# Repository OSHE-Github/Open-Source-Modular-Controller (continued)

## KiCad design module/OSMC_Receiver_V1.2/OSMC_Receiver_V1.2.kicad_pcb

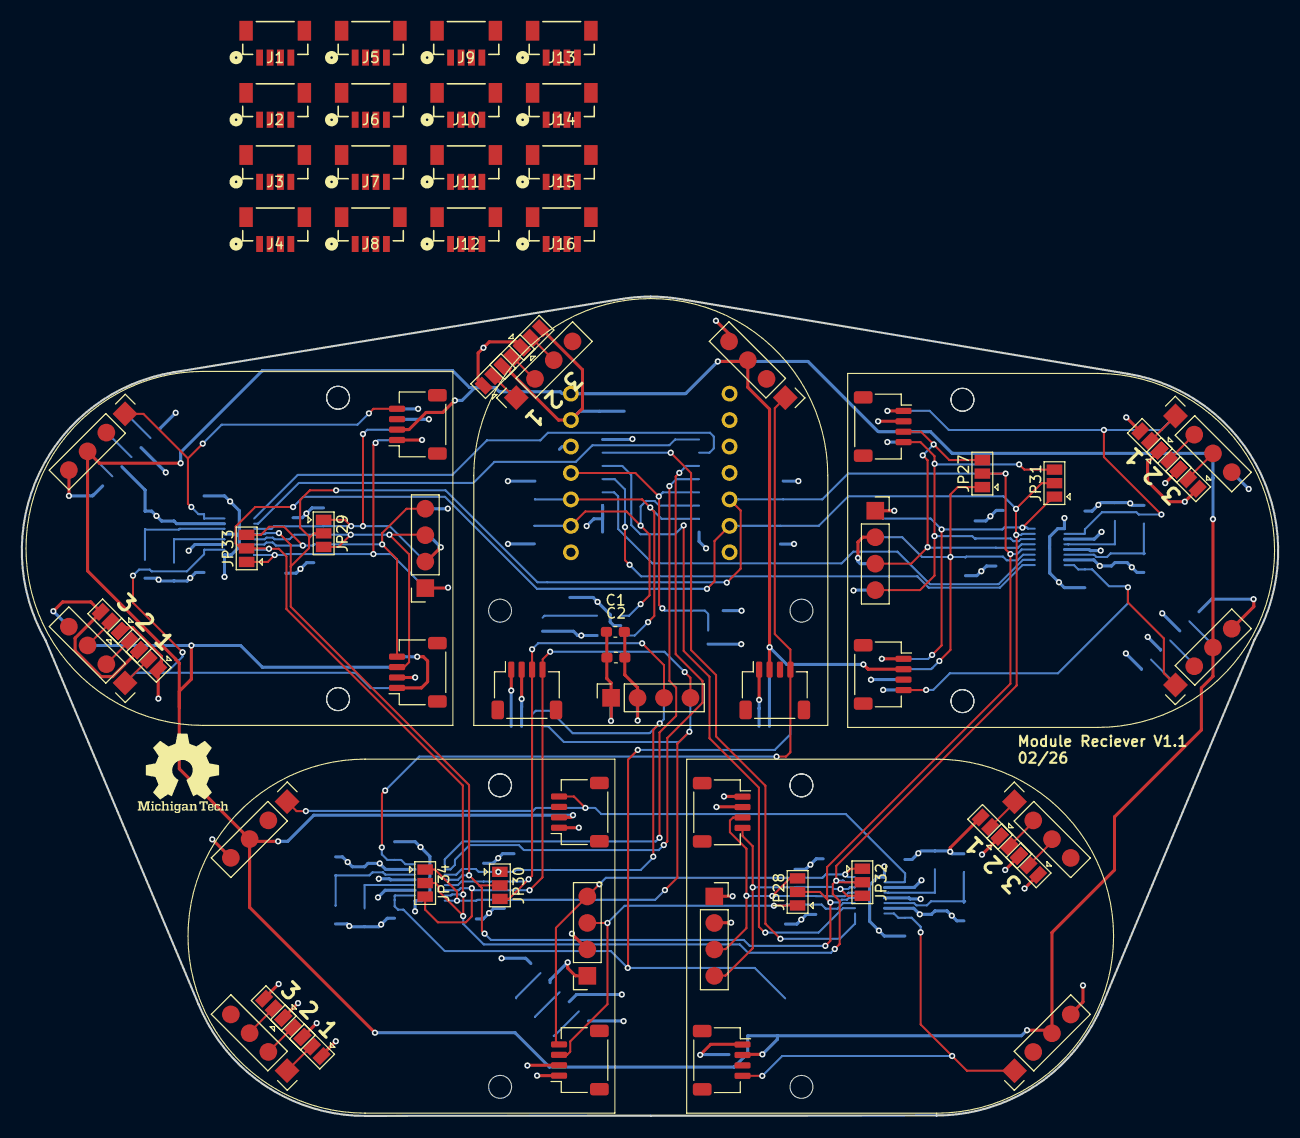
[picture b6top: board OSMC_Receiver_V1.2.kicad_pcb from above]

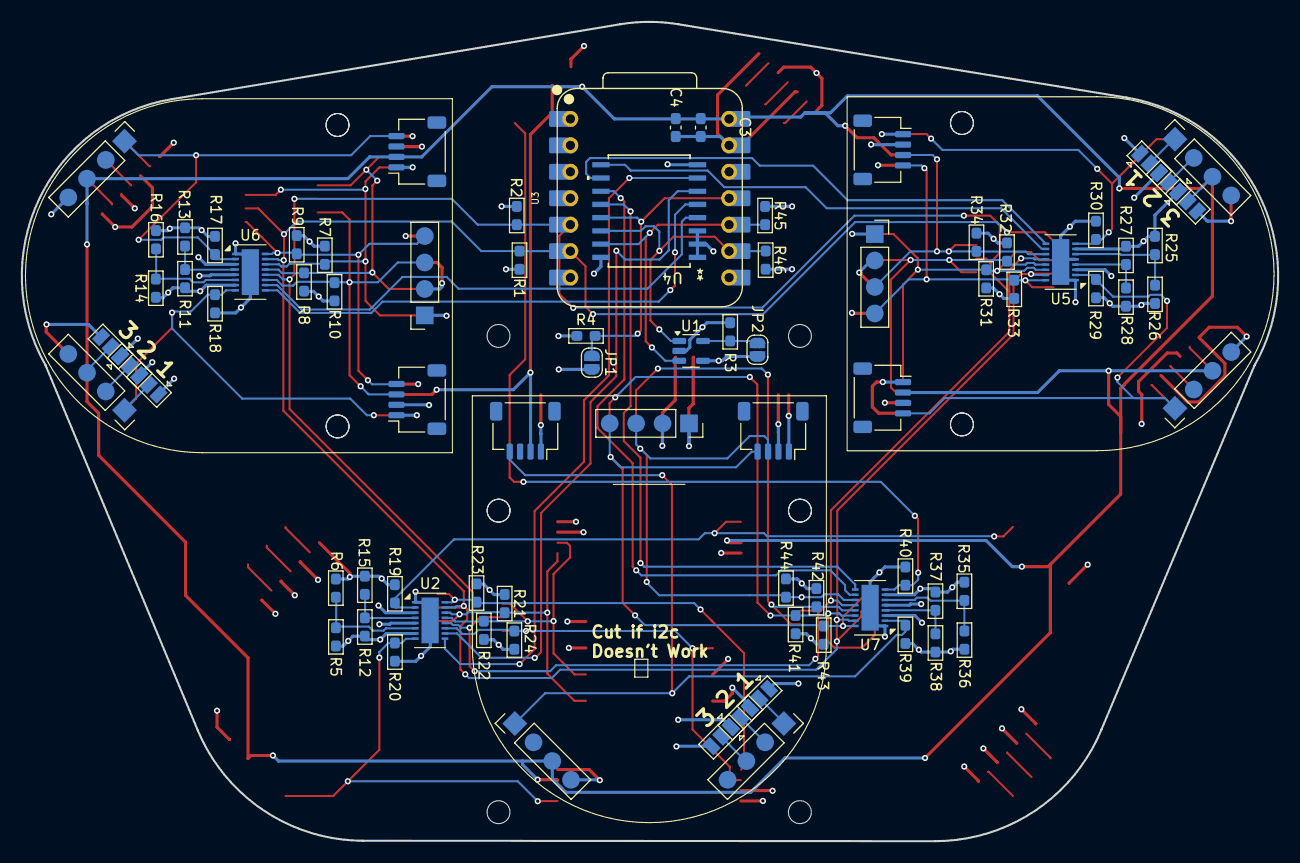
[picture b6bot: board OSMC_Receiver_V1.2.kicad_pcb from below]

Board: 4 copper layers, 120.7 x 78.7 mm, 115 parts (69 on the bottom side), 81 nets.

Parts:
C1, C2: .1 u; C_0603_1608Metric_Pad1.08x0.95mm_HandSolder
C3, C4: C; C_0603_1608Metric_Pad1.08x0.95mm_HandSolder
J1, J2, J3, J4, J5, J6, J7, J8, J9, J10, J11, J12, J13, J14, J15, J16: Conn_01x04; CONN4_BM04B-SRSS_JST
JP1: int; SolderJumper-2_P1.3mm_Open_RoundedPad1.0x1.5mm
JP2: WP; SolderJumper-2_P1.3mm_Open_RoundedPad1.0x1.5mm
JP3, JP4, JP5, JP6, JP7, JP8, JP9, JP10, JP11, JP12, JP13, JP14, JP15, JP16, JP17, JP18, JP19, JP20, JP21, JP22, JP23, JP24, JP25, JP26, JP27, JP28, JP29, JP30, JP31, JP32, JP33, JP34: SolderJumper_3_Open; SolderJumper-3_P1.3mm_Open_Pad1.0x1.5mm
R1, R2, R7, R8, R9, R10, R17, R18, R19, R20, R21, R22, R23, R24, R29, R30, R31, R32, R33, R34, R39, R40, R41, R42, R43, R44, R45, R46: 10k; R_0603_1608Metric_Pad1.05x0.95mm_HandSolder
R3, R4: 100k; R_0603_1608Metric_Pad1.05x0.95mm_HandSolder
R5, R11: 976k; R_0603_1608Metric_Pad1.05x0.95mm_HandSolder
R6: 182k; R_0603_1608Metric_Pad1.05x0.95mm_HandSolder
R12: 1M; R_0603_1608Metric_Pad1.05x0.95mm_HandSolder
R13: 102k; R_0603_1608Metric_Pad1.05x0.95mm_HandSolder
R14: R; R_0603_1608Metric_Pad1.05x0.95mm_HandSolder
R15: 280k; R_0603_1608Metric_Pad1.05x0.95mm_HandSolder
R16: 0; R_0603_1608Metric_Pad1.05x0.95mm_HandSolder
R25, R27, R35, R37: 1000k; R_0603_1608Metric_Pad1.05x0.95mm_HandSolder
R26: 392k; R_0603_1608Metric_Pad1.05x0.95mm_HandSolder
R28: 523k; R_0603_1608Metric_Pad1.05x0.95mm_HandSolder
R36: 681k; R_0603_1608Metric_Pad1.05x0.95mm_HandSolder
R38: 887k; R_0603_1608Metric_Pad1.05x0.95mm_HandSolder
U1: 24AA02-OT; SOT-23-5
U2, U5, U6, U7: LTC4317; DFN-16-1EP_3x5mm_P0.5mm_EP1.66x4.4mm
U3: XIAO-ESP32-S3-DIP
U4: PCF8574DWR; DW16-L
U13, U14, U15, U16, U17, U18, U19, U20: OSMC Module Board; Module standard pin large outline

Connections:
+5V: C3.1, C4.1, J2.3, J4.3, J6.3, J8.3, J10.3, J12.3, J14.3, J16.3, U3.14 (5V), U13.10 (5V), U13.15 (5V), U14.10 (5V), U14.15 (5V), U15.10 (5V), U15.15 (5V), U16.10 (5V), U16.15 (5V), U17.10 (5V), U17.15 (5V), U18.10 (5V), U18.15 (5V), U19.10 (5V), U19.15 (5V), U20.10 (5V), U20.15 (5V)
/INT: JP1.1 (A), R4.2, U3.11 (PA6_A10_D10_MOSI), U4.13 (~INT)
/Modules/Board attachment/Opt0: J2.2, U13.11 (OPT), U13.14 (OPT)
/Modules/Board attachment/Opt1: J4.2, U15.11 (OPT), U15.14 (OPT)
/Modules/Board attachment/Opt2: J6.2, U16.11 (OPT), U16.14 (OPT)
/Modules/Board attachment/Opt3: J8.2, U18.11 (OPT), U18.14 (OPT)
/Modules/Board attachment/Opt4: J14.2, U17.11 (OPT), U17.14 (OPT)
/Modules/Board attachment/Opt5: J12.2, U20.11 (OPT), U20.14 (OPT)
/Modules/Board attachment/Opt6: J10.2, U14.11 (OPT), U14.14 (OPT)
/Modules/Board attachment/Opt7: J16.2, U19.11 (OPT), U19.14 (OPT)
/Modules/EN0: J2.1, R18.2, U6.8 (ENABLE1), U13.12 (Det), U13.13 (Det)
/Modules/EN1: J4.1, R17.2, U6.2 (ENABLE2), U15.12 (Det), U15.13 (Det)
/Modules/EN2: J6.1, R20.2, U2.8 (ENABLE1), U16.12 (Det), U16.13 (Det)
/Modules/EN3: J8.1, R19.2, U2.2 (ENABLE2), U18.12 (Det), U18.13 (Det)
/Modules/EN4: J14.1, R30.2, U5.8 (ENABLE1), U17.12 (Det), U17.13 (Det)
/Modules/EN5: J12.1, R29.2, U5.2 (ENABLE2), U20.12 (Det), U20.13 (Det)
/Modules/EN6: J10.1, R40.2, U7.8 (ENABLE1), U14.12 (Det), U14.13 (Det)
/Modules/EN7: J16.1, R39.2, U7.2 (ENABLE2), U19.12 (Det), U19.13 (Det)
/Modules/P0: U4.4 (P0), U6.10 (READY1)
/Modules/P1: U4.5 (P1), U6.9 (READY2)
/Modules/P2: U2.10 (READY1), U4.6 (P2)
/Modules/P3: U2.9 (READY2), U4.7 (P3)
/Modules/P4: U4.9 (P4), U5.10 (READY1)
/Modules/P5: U4.10 (P5), U5.9 (READY2)
/Modules/P6: U4.11 (P6), U7.10 (READY1)
/Modules/P7: U4.12 (P7), U7.9 (READY2)
/Modules/SCL0: J1.1, JP31.3 (B), R7.2, U6.14 (SCLOUT1), U13.4 (SCL), U13.8 (SCL)
/Modules/SCL1: J3.1, JP31.1 (A), R9.2, U6.16 (SCLOUT2), U15.4 (SCL), U15.8 (SCL)
/Modules/SCL2: J5.1, JP32.3 (B), R21.2, U2.14 (SCLOUT1), U16.4 (SCL), U16.8 (SCL)
/Modules/SCL3: J7.1, JP32.1 (A), R23.2, U2.16 (SCLOUT2), U18.4 (SCL), U18.8 (SCL)
/Modules/SCL4: J13.1, JP33.3 (B), R31.2, U5.14 (SCLOUT1), U17.4 (SCL), U17.8 (SCL)
/Modules/SCL5: J11.1, JP33.1 (A), R33.2, U5.16 (SCLOUT2), U20.4 (SCL), U20.8 (SCL)
/Modules/SCL6: J9.1, JP34.3 (B), R41.2, U7.14 (SCLOUT1), U14.4 (SCL), U14.8 (SCL)
/Modules/SCL7: J15.1, JP34.1 (A), R43.2, U7.16 (SCLOUT2), U19.4 (SCL), U19.8 (SCL)
/Modules/SDA0: J1.2, JP27.3 (B), R8.2, U6.13 (SDAOUT1), U13.3 (SDA), U13.7 (SDA)
/Modules/SDA1: J3.2, JP27.1 (A), R10.2, U6.11 (SDAOUT2), U15.3 (SDA), U15.7 (SDA)
/Modules/SDA2: J5.2, JP28.3 (B), R22.2, U2.13 (SDAOUT1), U16.3 (SDA), U16.7 (SDA)
/Modules/SDA3: J7.2, JP28.1 (A), R24.2, U2.11 (SDAOUT2), U18.3 (SDA), U18.7 (SDA)
/Modules/SDA4: J13.2, JP29.3 (B), R32.2, U5.13 (SDAOUT1), U17.3 (SDA), U17.7 (SDA)
/Modules/SDA5: J11.2, JP29.1 (A), R34.2, U5.11 (SDAOUT2), U20.3 (SDA), U20.7 (SDA)
/Modules/SDA6: J9.2, JP30.3 (B), R42.2, U7.13 (SDAOUT1), U14.3 (SDA), U14.7 (SDA)
/Modules/SDA7: J15.2, JP30.1 (A), R44.2, U7.11 (SDAOUT2), U19.3 (SDA), U19.7 (SDA)
/SCL: JP31.2 (C), JP32.2 (C), JP33.2 (C), JP34.2 (C), R1.2, U2.15 (SCLIN), U3.6 (PA9_A5_D5_SCL), U5.15 (SCLIN), U6.15 (SCLIN), U7.15 (SCLIN)
/SCL1: R46.2, U1.1 (SCL), U3.9 (PA7_A8_D8_SCK), U4.14 (SCL)
/SDA: JP27.2 (C), JP28.2 (C), JP29.2 (C), JP30.2 (C), R2.2, U2.12 (SDAIN), U3.5 (PA8_A4_D4_SDA), U5.12 (SDAIN), U6.12 (SDAIN), U7.12 (SDAIN)
/SDA1: R45.2, U1.3 (SDA), U3.10 (PA5_A9_D9_MISO), U4.15 (SDA)
/wp: JP2.1 (A), R3.2, U1.5 (WP)
GND: C1.2, C2.2, C3.2, C4.2, J1.4, J2.4, J3.4, J4.4, J5.4, J6.4, J7.4, J8.4, J9.4, J10.4, J11.4, J12.4, J13.4, J14.4, J15.4, J16.4, JP3.3 (B), JP4.3 (B), JP5.3 (B), JP6.3 (B), JP7.3 (B), JP8.3 (B), JP9.3 (B), JP10.3 (B), JP11.3 (B), JP12.3 (B), JP13.3 (B), JP14.3 (B), JP15.3 (B), JP16.3 (B), JP17.3 (B), JP18.3 (B), JP19.3 (B), JP20.3 (B), JP21.3 (B), JP22.3 (B), JP23.3 (B), JP24.3 (B), JP25.3 (B), JP26.3 (B), R3.1, R4.1, R6.2, R13.2, R15.2, R16.2, R17.1, R18.1, R19.1, R20.1, R26.2, R28.2, R29.1, R30.1, R36.2, R38.2, R39.1, R40.1, U1.2 (V_{SS}), U2.1 (GND), U2.3 (XORH2), U2.5 (XORH1), U2.17 (EP), U3.13 (GND), U4.1 (A0), U4.2 (A1), U4.3 (A2), U4.8 (GND), U5.1 (GND), U5.3 (XORH2), U5.5 (XORH1), U5.17 (EP), U6.1 (GND), U6.3 (XORH2), U6.5 (XORH1), U6.17 (EP), U7.1 (GND), U7.3 (XORH2), U7.5 (XORH1), U7.17 (EP), U13.1 (Gnd), U13.5 (Gnd), U13.9 (Gnd), U13.16 (GND), U14.1 (Gnd), U14.5 (Gnd), U14.9 (Gnd), U14.16 (GND), U15.1 (Gnd), U15.5 (Gnd), U15.9 (Gnd), U15.16 (GND), U16.1 (Gnd), U16.5 (Gnd), U16.9 (Gnd), U16.16 (GND), U17.1 (Gnd), U17.5 (Gnd), U17.9 (Gnd), U17.16 (GND), U18.1 (Gnd), U18.5 (Gnd), U18.9 (Gnd), U18.16 (GND), U19.1 (Gnd), U19.5 (Gnd), U19.9 (Gnd), U19.16 (GND), U20.1 (Gnd), U20.5 (Gnd), U20.9 (Gnd), U20.16 (GND)
unnamed: JP3.2 (C), U16.18 (A3)
unnamed: JP4.2 (C), U16.19 (A2)
unnamed: JP5.2 (C), U16.20 (A1)
unnamed: JP6.2 (C), U15.18 (A3)
unnamed: JP7.2 (C), U15.19 (A2)
unnamed: JP8.2 (C), U15.20 (A1)
unnamed: JP9.2 (C), U13.18 (A3)
unnamed: JP10.2 (C), U13.19 (A2)
unnamed: JP11.2 (C), U13.20 (A1)
unnamed: JP12.2 (C), U18.18 (A3)
unnamed: JP13.2 (C), U18.19 (A2)
unnamed: JP14.2 (C), U18.20 (A1)
unnamed: JP15.2 (C), U19.18 (A3)
unnamed: JP16.2 (C), U19.19 (A2)
unnamed: JP17.2 (C), U19.20 (A1)
unnamed: JP18.2 (C), U17.18 (A3)
unnamed: JP19.2 (C), U17.19 (A2)
unnamed: JP20.2 (C), U17.20 (A1)
unnamed: JP21.2 (C), U20.18 (A3)
unnamed: JP22.2 (C), U20.19 (A2)
unnamed: JP23.2 (C), U20.20 (A1)
unnamed: JP24.2 (C), U14.18 (A3)
unnamed: JP25.2 (C), U14.19 (A2)
unnamed: JP26.2 (C), U14.20 (A1)
unnamed: R5.2, R6.1, U2.6 (XORL1)
unnamed: R12.2, R15.1, U2.4 (XORL2)
unnamed: R25.2, R26.1, U5.6 (XORL1)
unnamed: R27.2, R28.1, U5.4 (XORL2)
unnamed: R14.2, R16.1, U6.6 (XORL1)
unnamed: R11.2, R13.1, U6.4 (XORL2)
unnamed: R35.2, R36.1, U7.6 (XORL1)
unnamed: R37.2, R38.1, U7.4 (XORL2)
VDD: C1.1, C2.1, J1.3, J3.3, J5.3, J7.3, J9.3, J11.3, J13.3, J15.3, JP1.2 (B), JP2.2 (B), JP3.1 (A), JP4.1 (A), JP5.1 (A), JP6.1 (A), JP7.1 (A), JP8.1 (A), JP9.1 (A), JP10.1 (A), JP11.1 (A), JP12.1 (A), JP13.1 (A), JP14.1 (A), JP15.1 (A), JP16.1 (A), JP17.1 (A), JP18.1 (A), JP19.1 (A), JP20.1 (A), JP21.1 (A), JP22.1 (A), JP23.1 (A), JP24.1 (A), JP25.1 (A), JP26.1 (A), R1.1, R2.1, R5.1, R7.1, R8.1, R9.1, R10.1, R11.1, R12.1, R14.1, R21.1, R22.1, R23.1, R24.1, R25.1, R27.1, R31.1, R32.1, R33.1, R34.1, R35.1, R37.1, R41.1, R42.1, R43.1, R44.1, R45.1, R46.1, U1.4 (V_{CC}), U2.7 (VCC), U3.12 (3V3), U4.16 (VDD), U5.7 (VCC), U6.7 (VCC), U7.7 (VCC), U13.2 (Vdd), U13.6 (Vdd), U14.2 (Vdd), U14.6 (Vdd), U15.2 (Vdd), U15.6 (Vdd), U16.2 (Vdd), U16.6 (Vdd), U17.2 (Vdd), U17.6 (Vdd), U18.2 (Vdd), U18.6 (Vdd), U19.2 (Vdd), U19.6 (Vdd), U20.2 (Vdd), U20.6 (Vdd)

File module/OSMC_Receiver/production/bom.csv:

Designator,Footprint,Quantity,Value,LCSC Part #
"C1, C2",0603,2,.1 u,
"C3, C4",0603,2,C,
"R1, R10, R17, R18, R19, R2, R20, R21, R22, R23, R24, R29, R30, R31, R32, R33, R34, R39, R40, R41, R42, R43, R44, R45, R46, R7, R8, R9",0603,28,10k,
"R11, R5",0603,2,976k,
"R12, R6",0603,2,182k,
R13,0603,1,102k,
R14,0603,1,R,
R15,0603,1,280k,
R16,0603,1,0,
"R25, R27, R35, R37",0603,4,1000k,
R26,0603,1,392k,
R28,0603,1,523k,
"R3, R4",0603,2,100k,
R36,0603,1,681k,
R38,0603,1,887k,
U1,SOT-23-5,1,24AA02-OT,
"U13, U14, U15, U16, U17, U18, U19, U20",Module standard pin large outline,8,OSMC Module Board,
"U2, U5, U6, U7",DFN-16-1EP_3x5mm_P0.5mm_EP1.66x4.4mm,4,LTC4317,
U3,XIAO-ESP32-S3-DIP,1,XIAO-ESP32-S3-DIP,
U4,DW16-L,1,PCF8574DWR,

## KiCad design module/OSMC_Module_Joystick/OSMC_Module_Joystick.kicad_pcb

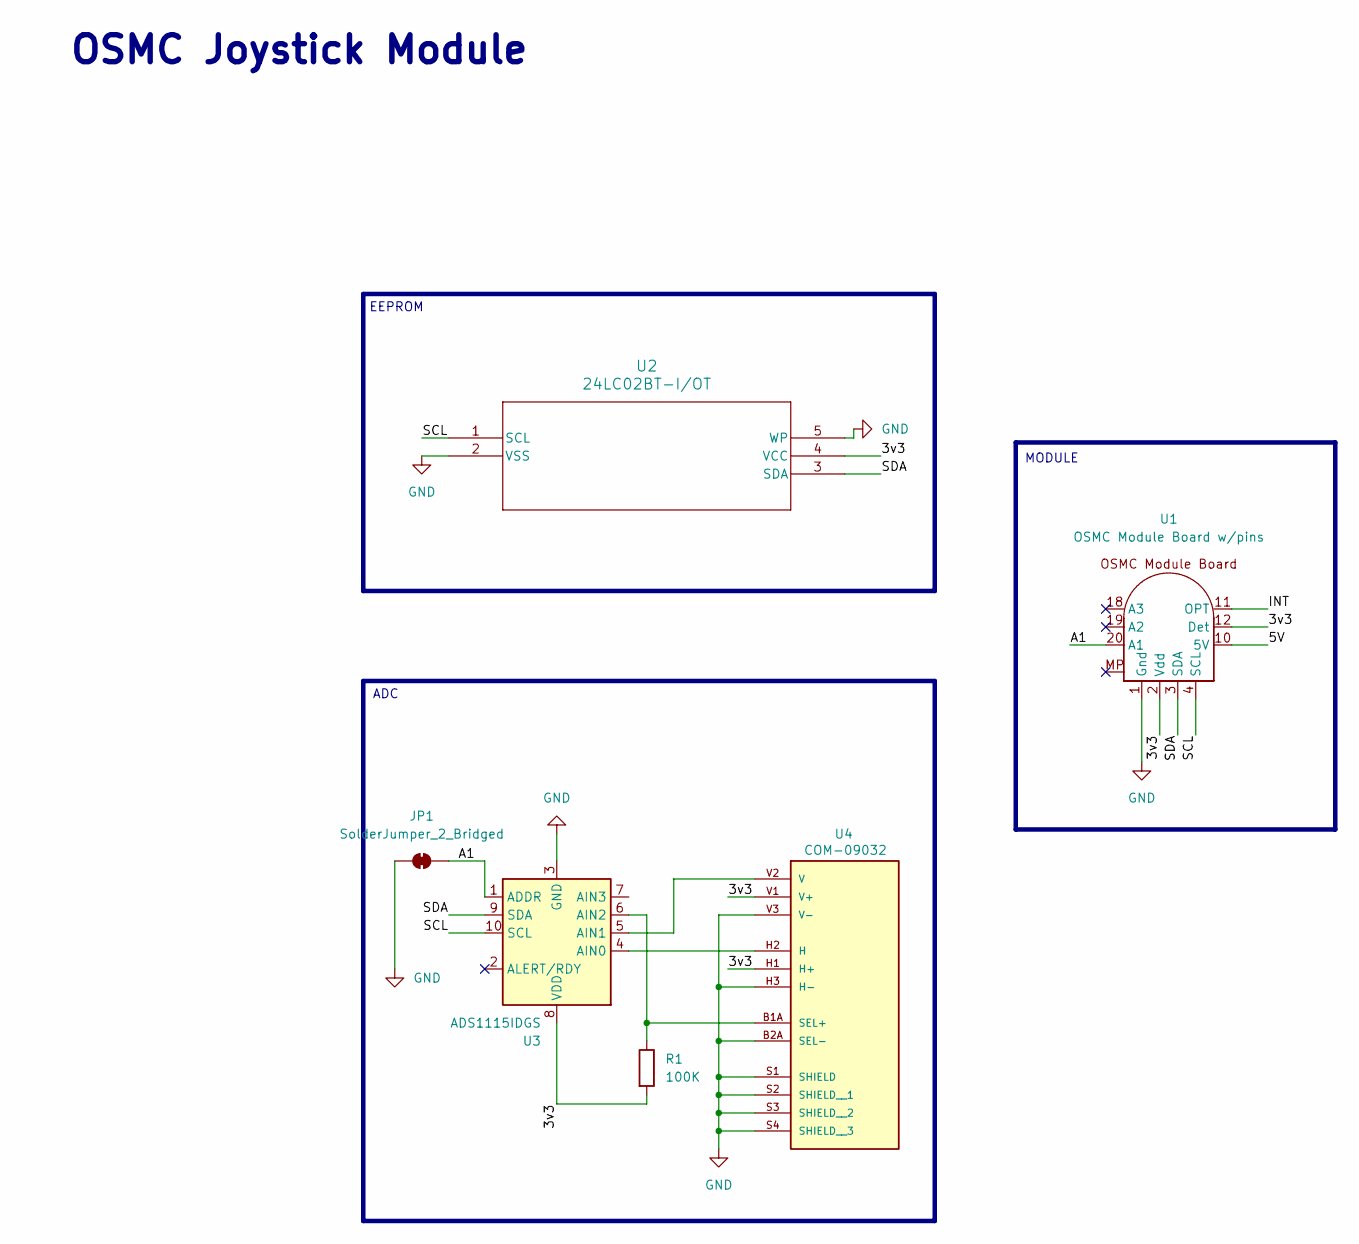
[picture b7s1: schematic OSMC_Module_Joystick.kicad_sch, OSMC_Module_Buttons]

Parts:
JP1: SolderJumper_2_Bridged; SolderJumper-2_P1.3mm_Bridged2Bar_RoundedPad1.0x1.5mm
R1: 100K; R_0603_1608Metric_Pad0.98x0.95mm_HandSolder
U1: OSMC Module Board w/pins; Module standard pin large
U2: 24LC02BT-I/OT; SOT-23-5_MC_MCH
U3: ADS1115IDGS; TSSOP-10_3x3mm_P0.5mm
U4: COM-09032; XDCR_COM-09032; PARTREV N/A

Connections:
/3v3: R1.2, U1.2 (Vdd), U1.6 (Vdd), U1.12 (Det), U1.13 (Int), U2.4 (VCC), U3.8 (VDD), U4.H1 (H+), U4.V1 (V+)
/5V: U1.10 (5V), U1.15 (5V)
/A1: JP1.2 (B), U1.20 (A1), U3.1 (ADDR)
/INT: U1.11 (OPT), U1.14 (OPT)
/SCL: U1.4 (SCL), U1.8 (SCL), U2.1 (SCL), U3.10 (SCL)
/SDA: U1.3 (SDA), U1.7 (SDA), U2.3 (SDA), U3.9 (SDA)
GND: JP1.1 (A), U1.1 (Gnd), U1.5 (Gnd), U1.9 (Gnd), U1.16 (GND), U2.2 (VSS), U2.5 (WP), U3.3 (GND), U4.B2A (SEL-), U4.B2B (SEL-), U4.H3 (H-), U4.S1 (SHIELD), U4.S2 (SHIELD__1), U4.S3 (SHIELD__2), U4.S4 (SHIELD__3), U4.V3 (V-)
unnamed: U3.4 (AIN0), U4.H2 (H)
unnamed: U3.5 (AIN1), U4.V2 (V)
unnamed: R1.1, U3.6 (AIN2), U4.B1A (SEL+), U4.B1B (SEL+)

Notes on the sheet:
EEPROM
ADC
OSMC Joystick Module
MODULE

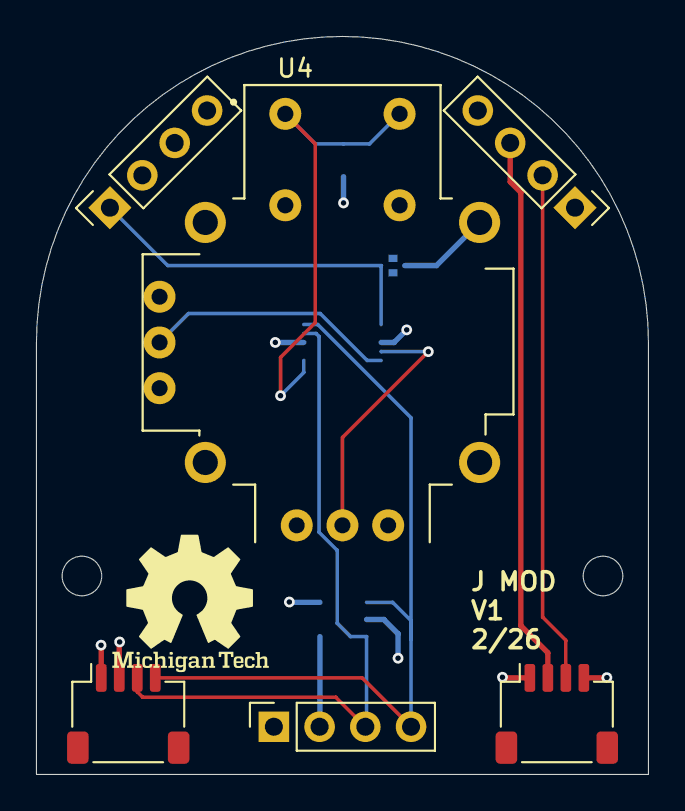
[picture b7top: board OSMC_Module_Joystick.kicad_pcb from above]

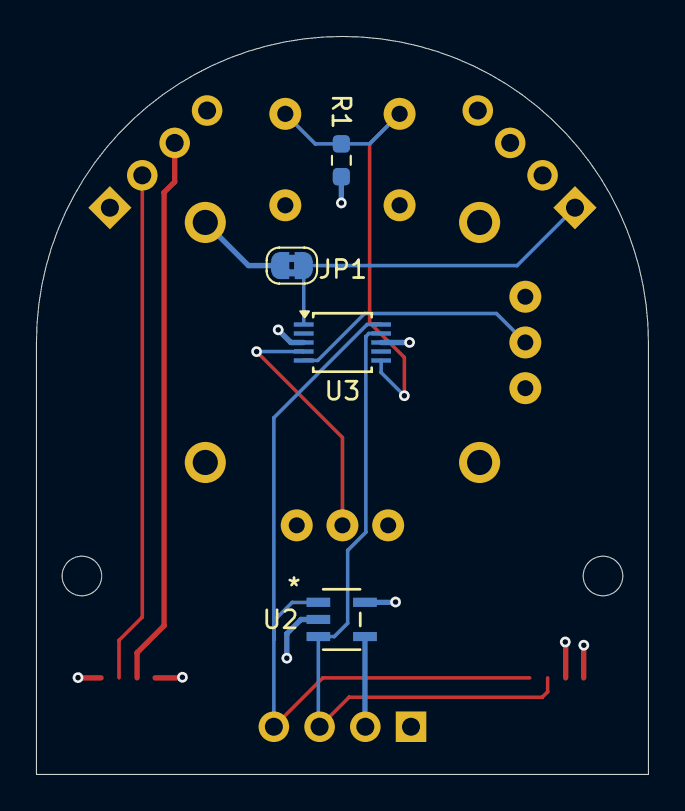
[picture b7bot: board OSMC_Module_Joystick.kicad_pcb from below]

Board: 4 copper layers, 34.0 x 41.0 mm, 6 parts (4 on the bottom side), 10 nets.

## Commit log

2025-09-09 code
2025-09-12 testing more code
2025-09-12 update code
2025-09-19 kicad model
2025-09-20 update pcb
2025-09-20 made new version
2025-09-20 removed un-need backups
2025-09-25 auto save
2025-09-25 .6 done
2025-09-26 updated carrier board
2025-09-26 unneed files
2025-09-26 updated liby used
2025-09-26 generated bom
2025-09-26 added logo and date
2025-09-26 centered components
2025-09-27 3d model
2025-10-03 slimed down files
2025-10-03 current PCBs
2025-10-09 Initial Module PCBs
2025-10-11 added test points
2025-10-11 trace update
2025-10-11 updated traces and labels
2025-10-11 trace
2025-10-11 updated footprints
2025-10-11 track update
2025-10-11 update tracks
2025-10-14 updated power trace for expansion
    made where there is 5v to carrier board for future batter expansion
2025-10-14 change pin headers
2025-10-14 update traces
2025-10-15 added mounting holes
2025-10-15 refile zones
2025-10-15 refill zones
2025-11-05 update boards for prodution
2025-12-02 Merged files for Semester 1
    All notable files from past branches merged to this one branch with the latest codes.
    For use next Semester and organization
2025-12-04 gerber files generated
2025-12-05 slim down
2025-12-05 more files
2025-12-06 Squashed commit of the following:
    commit bee188ac67190d8f69e02bf0fbf3a9b0818b590d
    Author: Koalaven <102919896+Koalaven@users.noreply.github.com>
    Date: Thu Dec 4 21:13:27 2025 -0500
    more files
    commit 6b35f9c097d493935acfd4adb1660864742cfc16
    Author: Koalaven <102919896+Koalaven@users.noreply.github.com>
2025-12-07 added READMEs
2026-01-16 module design
2026-01-21 module spec update
2026-01-23 updated templet and renamed lib files
2026-01-23 updated symbol
2026-01-24 update footprints
2026-01-24 footprint rename
2026-01-28 started routing
2026-02-09 added module boards
2026-02-09 completed receiver board w/ translators
2026-02-11 reviewed PCBs
2026-02-11 cleared via and traces
2026-02-11 reorganized
2026-02-13 modules completed
2026-02-18 update to modules gerbers produced
2026-02-23 Create OSMC_Shell2.stl
    First version of the shell - still needs room for the bottom module, hole for wired connection, and holes for leds
2026-02-26 fixed diode direction
2026-02-27 created all gerber zips
2026-03-09 consolidated button and nav boards into one
2026-03-12 update resistor value
2026-03-12 more hand solderable joystick
2026-03-30 update to pcb, fixed i2c lines for bus 0 and 1
2026-03-31 code for controller and flash settings
    working code for controller
2026-03-31 board update
2026-04-01 Add files via upload
    Adding the case STLs for the modules and the alternate controller case.
2026-04-03 fix to read both joysticks
2026-04-14 Added shell files
2026-04-22 organizing
2026-04-22 Update Assembly guide.md
    Expanded the Shell printing section
    Updated the case assembly sectoin
2026-04-22 Update Assembly guide.md
    Fixed my broken links
2026-04-22 removed redundent connectors
2026-04-22 remove connectors
2026-04-23 Project Report
2026-04-23 renamed
